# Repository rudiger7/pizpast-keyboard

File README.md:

# PizPast Keyboard

A 59-key keyboard: custom KiCad PCB, RP2040-Zero, MX switches, 3D-printed case and keycaps, QMK + Vial firmware.

It works with the **standard** OS layout (US-International, Italian or UK extended) on Windows and Linux. No custom layout to install: the firmware decides what every key sends, including with Shift and AltGr.

## Repo layout

```
hardware/
  kicad/          schematic, PCB, JLCPCB production files
  layout/         keyboard-layout-editor files (kle-layout.json is current), ai03 plate.dxf
case/
  legacy-fusion/  old Fusion 360 STLs (to be replaced by a FreeCAD model)
keycaps/
  legacy/         old printable keycaps + legend SVGs
firmware/
  pizpast/ol/     QMK keyboard (copied into vial-qmk at build time)
docs/
  translator.md   how the Shift / AltGr tables work
  legacy-windows-layout/   the old .klc Windows layouts (no longer needed)
tools/build.sh    local build
tools/github-build.yml   GitHub Actions build -> move to .github/workflows/build.yml
```

## Firmware

| File | OS layout to select |
|---|---|
| `pizpast_ol_us_intl.uf2` | English (US, International) / Linux: "English (US, intl., with dead keys)" |
| `pizpast_ol_it.uf2` | Italian |
| `pizpast_ol_uk.uf2` | Windows: "United Kingdom Extended" / Linux: "English (UK, extended, Windows)". The plain UK layout also types the keycap legends. |

### Flash

1. Hold **ESC** while plugging in the keyboard (or hold BOOT on the RP2040-Zero). A drive called `RPI-RP2` appears.
2. Copy the `.uf2` onto it. The keyboard reboots.

### Build

- **GitHub:** every push builds the three files. Download them from the Actions run ("Artifacts").
- **Locally:** set up [vial-qmk](https://github.com/vial-kb/vial-qmk) with `qmk setup` (Linux/WSL) or QMK MSYS (Windows), then run `VIAL_QMK=~/vial-qmk tools/build.sh`. Output goes in `build/`.

The keyboard code lives only in this repo. vial-qmk is used unmodified, pinned in the GitHub workflow.

### Configure

Open [Vial](https://get.vial.today/). Unlock with **ESC + bottom-right key**. Layers 1-3 are the Shift / AltGr translation tables, layer 4 is Fn. See [docs/translator.md](docs/translator.md).

## Hardware

- Matrix 5x12, COL2ROW, 1N4148 diodes
- Cols: GP5 GP6 GP15 GP26 GP27 GP28 GP29 GP4 GP3 GP2 GP1 GP0
- Rows: GP13 GP14 GP9 GP8 GP7
- PCB 3D model: export from KiCad (`File > Export > STEP`). It's not in git because it's 37 MB.

## License

GPL-3.0-or-later. See [LICENSE](LICENSE).

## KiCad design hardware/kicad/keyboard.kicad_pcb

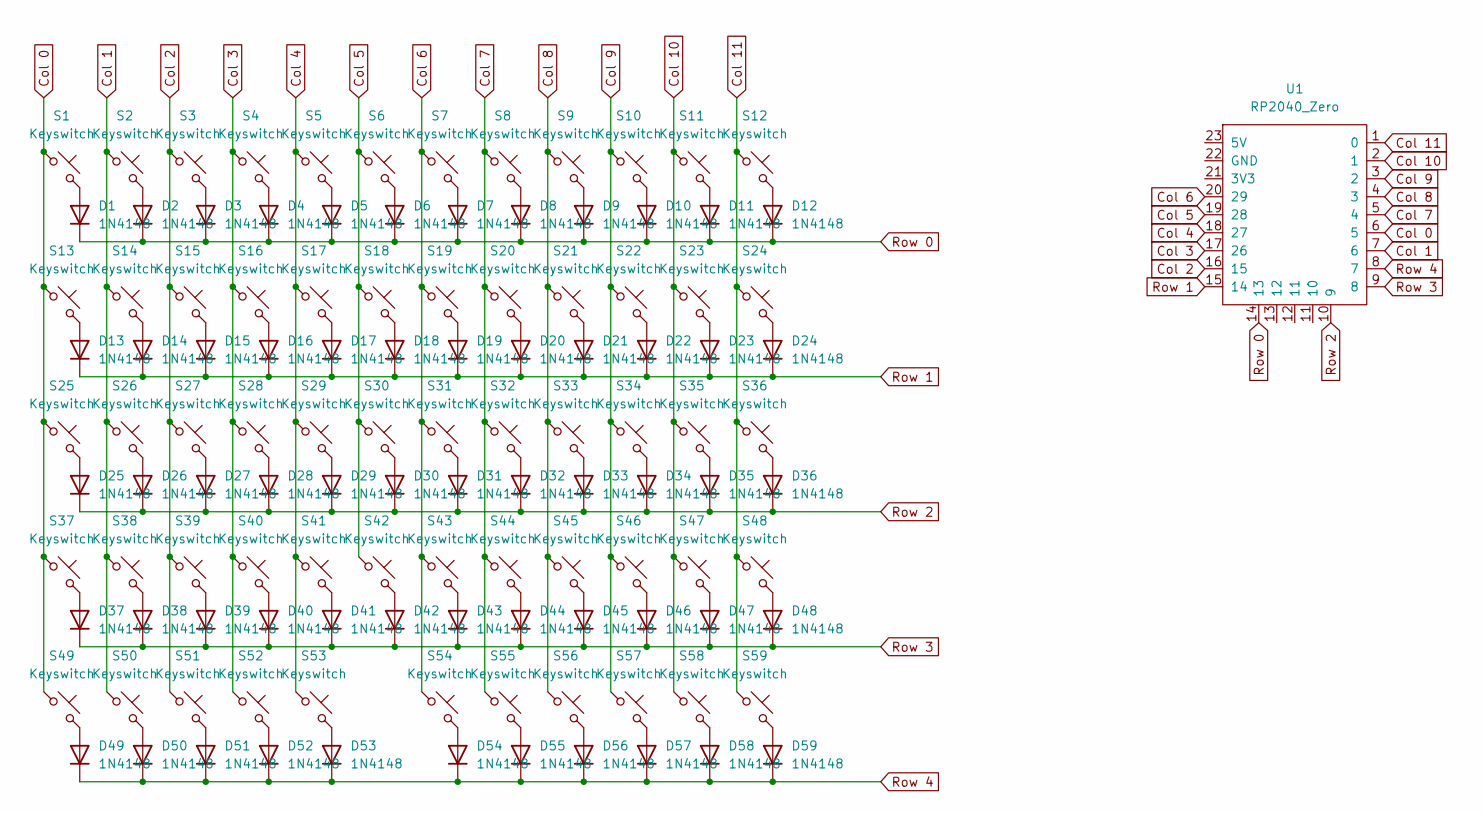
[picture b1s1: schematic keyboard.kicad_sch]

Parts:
D1, D2, D3, D4, D5, D6, D7, D8, D9, D10, D11, D12, D13, D14, D15, D16, D17, D18, D19, D20, D21, D22, D23, D24, D25, D26, D27, D28, D29, D30, D31, D32, D33, D34, D35, D36, D37, D38, D39, D40, D41, D42, D43, D44, D45, D46, D47, D48, D49, D50, D51, D52, D53, D54, D55, D56, D57, D58, D59: 1N4148; D_DO-35_SOD27_P7.62mm_Horizontal
S1, S2, S3, S4, S5, S6, S7, S8, S9, S10, S11, S12, S13, S14, S15, S16, S17, S18, S19, S20, S21, S22, S23, S24, S25, S26, S27, S28, S29, S30, S31, S32, S33, S34, S35, S36, S37, S38, S39, S40, S41, S42, S43, S44, S45, S46, S47, S48, S49, S50, S51, S52, S55, S56, S57, S58, S59: Keyswitch; MX_PCB_1.00u
S53, S54: Keyswitch; MX_PCB_1.50u
U1: RP2040_Zero

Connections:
Col 0: S1.1, S13.1, S25.1, S37.1, S49.1, U1.6 (5)
Col 1: S2.1, S14.1, S26.1, S38.1, S50.1, U1.7 (6)
Col 2: S3.1, S15.1, S27.1, S39.1, S51.1, U1.16 (15)
Col 3: S4.1, S16.1, S28.1, S40.1, S52.1, U1.17 (26)
Col 4: S5.1, S17.1, S29.1, S41.1, S53.1, U1.18 (27)
Col 5: S6.1, S18.1, S30.1, S42.1, U1.19 (28)
Col 6: S7.1, S19.1, S31.1, S43.1, S54.1, U1.20 (29)
Col 7: S8.1, S20.1, S32.1, S44.1, S55.1, U1.5 (4)
Col 8: S9.1, S21.1, S33.1, S45.1, S56.1, U1.4 (3)
Col 9: S10.1, S22.1, S34.1, S46.1, S57.1, U1.3 (2)
Col 10: S11.1, S23.1, S35.1, S47.1, S58.1, U1.2 (1)
Col 11: S12.1, S24.1, S36.1, S48.1, S59.1, U1.1 (0)
unnamed: D1.2 (A), S1.2
unnamed: D2.2 (A), S2.2
unnamed: D3.2 (A), S3.2
unnamed: D4.2 (A), S4.2
unnamed: D5.2 (A), S5.2
unnamed: D6.2 (A), S6.2
unnamed: D7.2 (A), S7.2
unnamed: D8.2 (A), S8.2
unnamed: D9.2 (A), S9.2
unnamed: D10.2 (A), S10.2
unnamed: D11.2 (A), S11.2
unnamed: D12.2 (A), S12.2
unnamed: D13.2 (A), S13.2
unnamed: D14.2 (A), S14.2
unnamed: D15.2 (A), S15.2
unnamed: D16.2 (A), S16.2
unnamed: D17.2 (A), S17.2
unnamed: D18.2 (A), S18.2
unnamed: D19.2 (A), S19.2
unnamed: D20.2 (A), S20.2
unnamed: D21.2 (A), S21.2
unnamed: D22.2 (A), S22.2
unnamed: D23.2 (A), S23.2
unnamed: D24.2 (A), S24.2
unnamed: D25.2 (A), S25.2
unnamed: D26.2 (A), S26.2
unnamed: D27.2 (A), S27.2
unnamed: D28.2 (A), S28.2
unnamed: D29.2 (A), S29.2
unnamed: D30.2 (A), S30.2
unnamed: D31.2 (A), S31.2
unnamed: D32.2 (A), S32.2
unnamed: D33.2 (A), S33.2
unnamed: D34.2 (A), S34.2
unnamed: D35.2 (A), S35.2
unnamed: D36.2 (A), S36.2
unnamed: D37.2 (A), S37.2
unnamed: D38.2 (A), S38.2
unnamed: D39.2 (A), S39.2
unnamed: D40.2 (A), S40.2
unnamed: D41.2 (A), S41.2
unnamed: D42.2 (A), S42.2
unnamed: D43.2 (A), S43.2
unnamed: D44.2 (A), S44.2
unnamed: D45.2 (A), S45.2
unnamed: D46.2 (A), S46.2
unnamed: D47.2 (A), S47.2
unnamed: D48.2 (A), S48.2
unnamed: D49.2 (A), S49.2
unnamed: D50.2 (A), S50.2
unnamed: D51.2 (A), S51.2
unnamed: D52.2 (A), S52.2
unnamed: D53.2 (A), S53.2
unnamed: D54.2 (A), S54.2
unnamed: D55.2 (A), S55.2
unnamed: D56.2 (A), S56.2
unnamed: D57.2 (A), S57.2
unnamed: D58.2 (A), S58.2
unnamed: D59.2 (A), S59.2
Row 0: D1.1 (K), D2.1 (K), D3.1 (K), D4.1 (K), D5.1 (K), D6.1 (K), D7.1 (K), D8.1 (K), D9.1 (K), D10.1 (K), D11.1 (K), D12.1 (K), U1.14 (13)
Row 1: D13.1 (K), D14.1 (K), D15.1 (K), D16.1 (K), D17.1 (K), D18.1 (K), D19.1 (K), D20.1 (K), D21.1 (K), D22.1 (K), D23.1 (K), D24.1 (K), U1.15 (14)
Row 2: D25.1 (K), D26.1 (K), D27.1 (K), D28.1 (K), D29.1 (K), D30.1 (K), D31.1 (K), D32.1 (K), D33.1 (K), D34.1 (K), D35.1 (K), D36.1 (K), U1.10 (9)
Row 3: D37.1 (K), D38.1 (K), D39.1 (K), D40.1 (K), D41.1 (K), D42.1 (K), D43.1 (K), D44.1 (K), D45.1 (K), D46.1 (K), D47.1 (K), D48.1 (K), U1.9 (8)
Row 4: D49.1 (K), D50.1 (K), D51.1 (K), D52.1 (K), D53.1 (K), D54.1 (K), D55.1 (K), D56.1 (K), D57.1 (K), D58.1 (K), D59.1 (K), U1.8 (7)

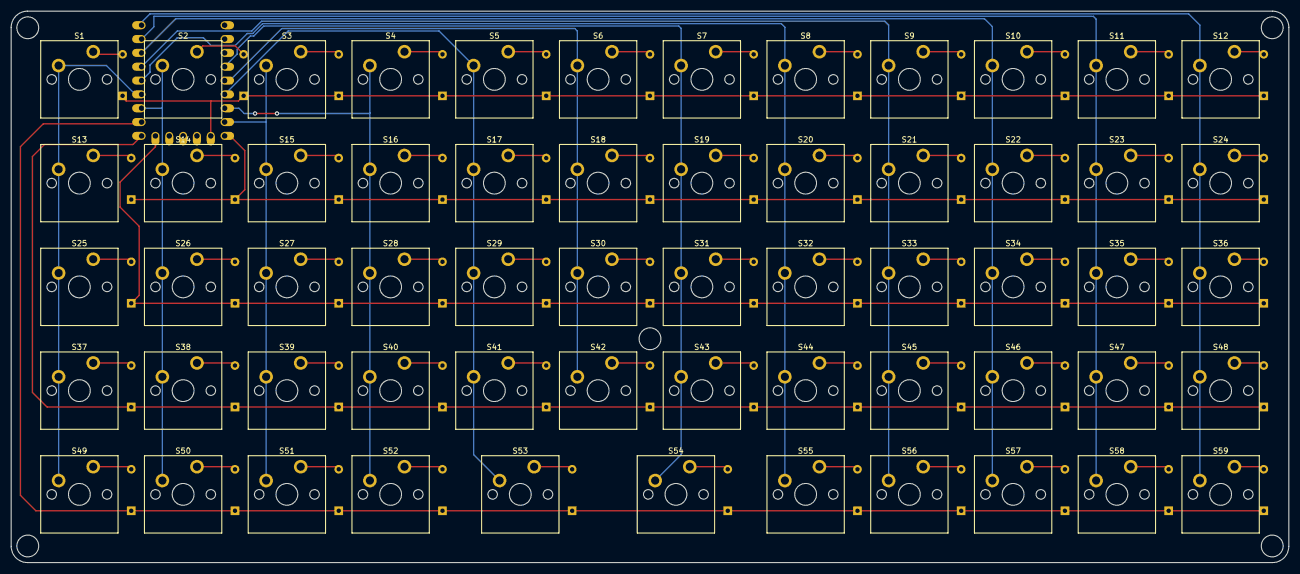
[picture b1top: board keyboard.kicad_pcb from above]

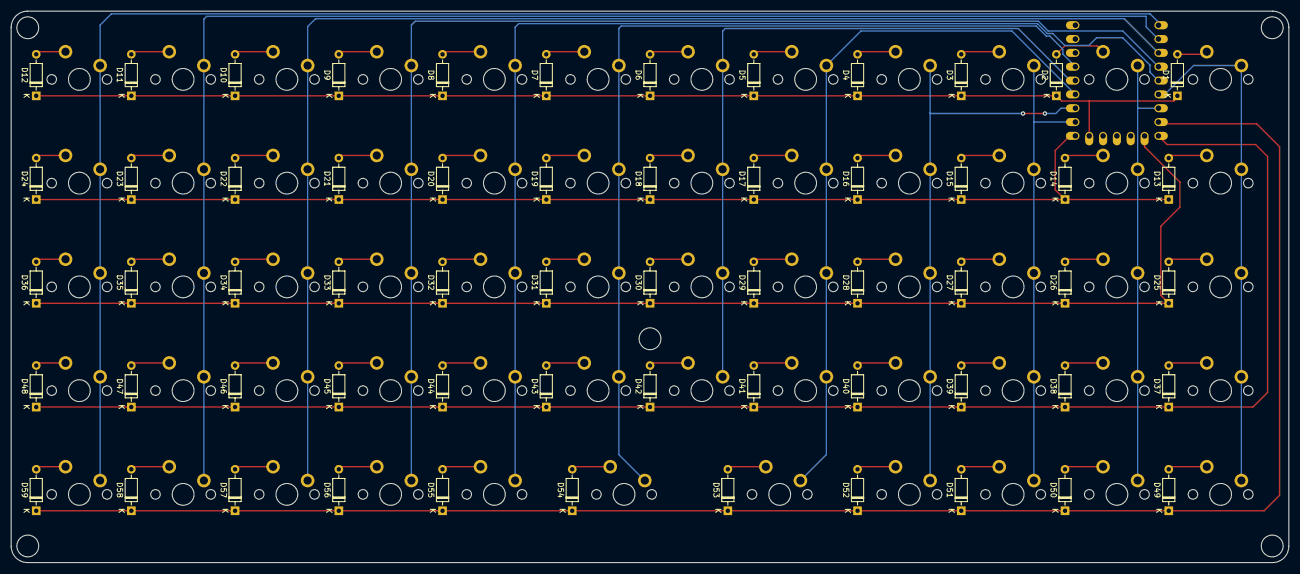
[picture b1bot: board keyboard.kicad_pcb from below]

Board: 2 copper layers, 234.6 x 101.2 mm, 119 parts (60 on the bottom side), 76 nets.

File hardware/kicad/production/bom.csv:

Designator,Footprint,Quantity,Value,LCSC Part #
"D1, D10, D11, D12, D13, D14, D15, D16, D17, D18, D19, D2, D20, D21, D22, D23, D24, D25, D26, D27, D28, D29, D3, D30, D31, D32, D33, D34, D35, D36, D37, D38, D39, D4, D40, D41, D42, D43, D44, D45, D46, D47, D48, D49, D5, D50, D51, D52, D53, D54, D55, D56, D57, D58, D59, D6, D7, D8, D9",D_DO-35_SOD27_P7.62mm_Horizontal,59,1N4148,
"S1, S10, S11, S12, S13, S14, S15, S16, S17, S18, S19, S2, S20, S21, S22, S23, S24, S25, S26, S27, S28, S29, S3, S30, S31, S32, S33, S34, S35, S36, S37, S38, S39, S4, S40, S41, S42, S43, S44, S45, S46, S47, S48, S49, S5, S50, S51, S52, S55, S56, S57, S58, S59, S6, S7, S8, S9",MX_PCB_1.00u,57,Keyswitch,
"S53, S54",MX_PCB_1.50u,2,Keyswitch,
U1,RP2040_Zero,1,RP2040_Zero,
